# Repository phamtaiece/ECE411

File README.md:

# ECE411
This is for ECE411 practicum. 
The project idea is where we post our idea. Come and contribute and have fun.

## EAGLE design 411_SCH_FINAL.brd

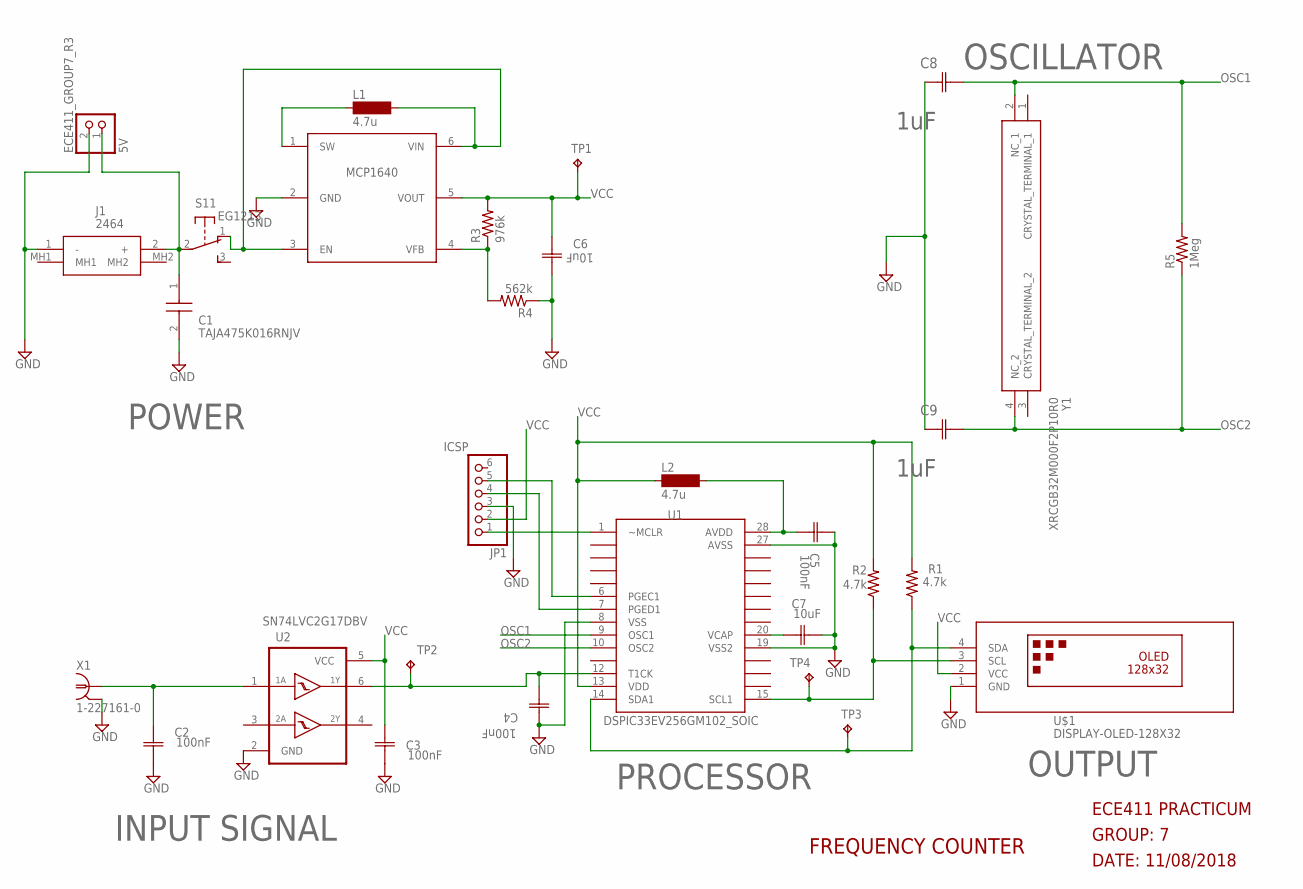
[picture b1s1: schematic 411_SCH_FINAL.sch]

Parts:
C1: TAJA475K016RNJV; CAPPM3216X180N
C2, C3, C4, C5: 100nF; CAPC2013X110N
C6, C7: 10uF; CAPC2013X140N
C8, C9: 1uF; CAPC2013X110N
ECE411_GROUP7_R3: 5V; JST-PH-2-THM-RA; MPN M20-9990246
J1: 2464
JP1: ICSP; 1X06
L1, L2: 4.7u; SM-1206
MCP1: MCP1640; SOP95P270X145-6; MPN MCP1640DT-I/CHY
R1, R2: 4.7k; M2012; MPN CR1206-JW-114ELF
R3: 976k; R0805
R4: 562k; R0805
R5: 1Meg; M0805
S1: EG1213
TP1, TP2, TP3, TP4: TPB1,27; B1,27
U1: DSPIC33EV256GM102_SOIC; SOIC127P1020X265-28; MPN DSPIC33EV256GM102
U2: SN74LVC2G17DBV; SOT23-6; MPN NC7WZ14P6X
U$1: DISPLAY-OLED-128X32; MPN SSD1306
X1: 1-227161-0; AMP_227161
Y1: XRCGB32M000F2P10R0; XRCGB32_F

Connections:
BATT: L1.2, MCP1.3 (EN), MCP1.6 (VIN), S1.1 (O)
GND: C1.2 (-), C2.2 (C2), C3.2 (C2), C4.2 (C2), C5.1 (C1), C6.2 (C2), C7.2 (C2), C8.1 (C1), C9.1 (C1), ECE411_GROUP7_R3.2 (1), J1.1 (-), JP1.3, MCP1.2 (GND), R4.1, U1.8 (VSS), U1.19 (VSS2), U1.27 (AVSS), U2.2 (GND), U$1.1 (GND), X1.2
unnamed: C7.1 (C1), U1.20 (VCAP)
unnamed: C1.1 (+), ECE411_GROUP7_R3.1 (2), J1.2 (+), S1.2
unnamed: R1.1, TP3.TP, U1.14 (SDA1), U$1.4 (SDA)
unnamed: C2.1 (C1), U2.1 (1A), X1.1
unnamed: C5.2 (C2), L2.2, U1.28 (AVDD)
unnamed: L1.1, MCP1.1 (SW)
unnamed: MCP1.4 (VFB), R3.1, R4.2
unnamed: JP1.1, U1.1 (~MCLR)
unnamed: R2.1, TP4.TP, U1.15 (SCL1), U$1.3 (SCL)
unnamed: JP1.4, U1.7 (PGED1)
unnamed: JP1.5, U1.6 (PGEC1)
unnamed: C4.1 (C1), TP2.TP, U1.12 (T1CK), U2.6 (1Y)
OSC1: C8.2 (C2), R5.2, U1.9 (OSC1), Y1.2 (NC_1)
OSC2: C9.2 (C2), R5.1, U1.10 (OSC2), Y1.4 (NC_2)
VCC: C3.1 (C1), C6.1 (C1), JP1.2, L2.1, MCP1.5 (VOUT), R1.2, R2.2, R3.2, TP1.TP, U1.13 (VDD), U2.5 (VCC), U$1.2 (VCC)

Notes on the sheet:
GROUP: 7
DATE: 11/08/2018
FREQUENCY COUNTER
ECE411 PRACTICUM
POWER
INPUT SIGNAL
OUTPUT
PROCESSOR
OSCILLATOR

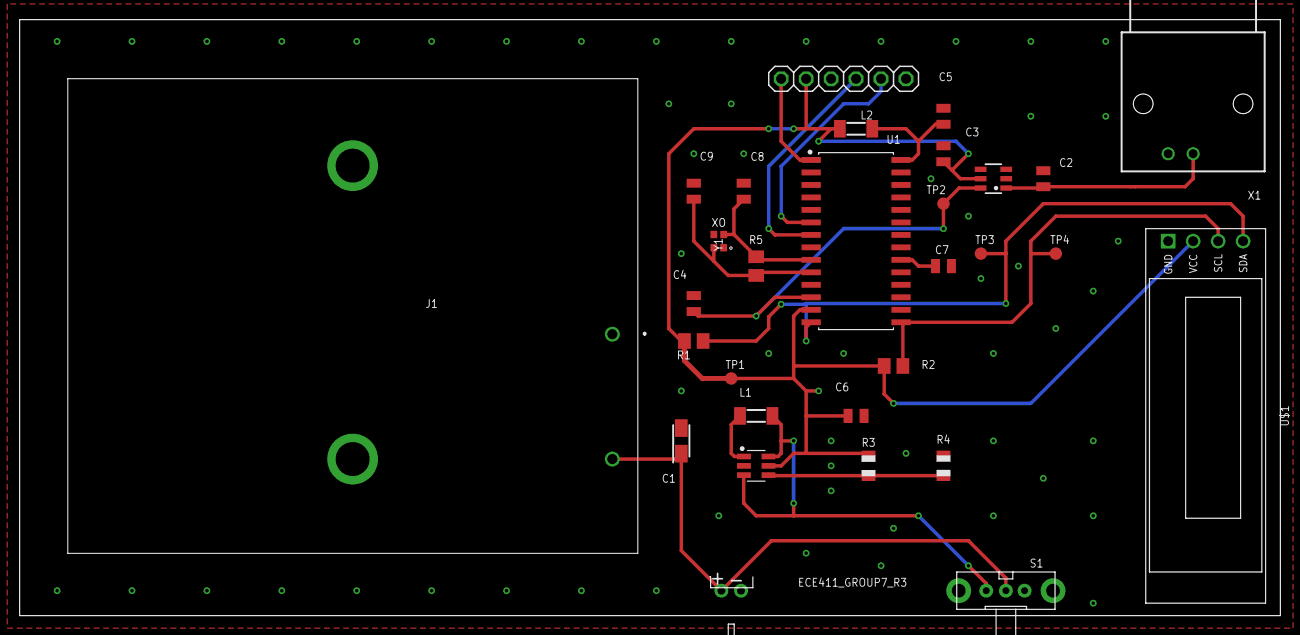
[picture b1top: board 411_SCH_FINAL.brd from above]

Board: 2 copper layers, 128.2 x 60.6 mm, 30 parts (0 on the bottom side), 17 nets.

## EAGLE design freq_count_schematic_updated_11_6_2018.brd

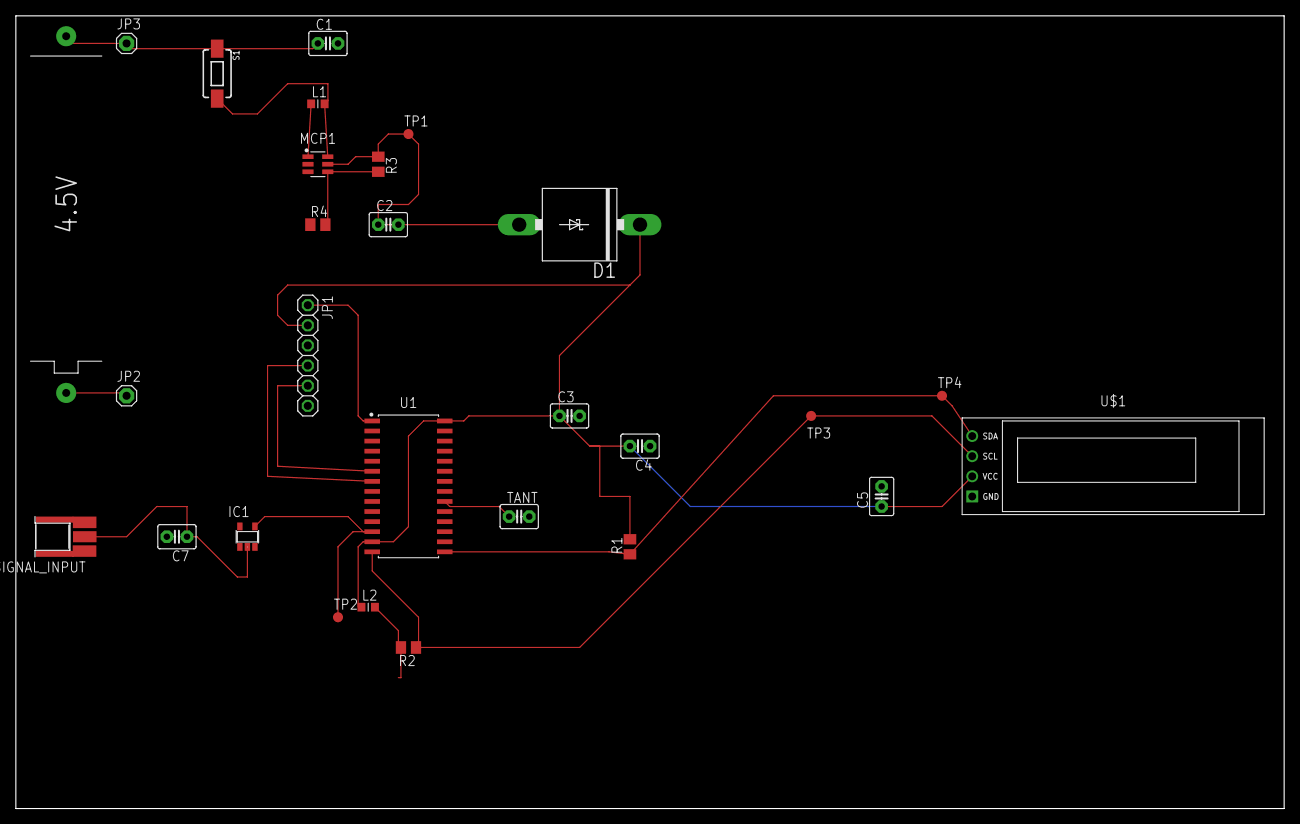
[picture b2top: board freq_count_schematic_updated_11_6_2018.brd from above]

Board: 2 copper layers, 160.0 x 100.0 mm, 28 parts (0 on the bottom side), 15 nets.

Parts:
4.5V: AAA; 12BH412
C1: 4.7u; C2.5-3
C2: 10u; C2.5-3
C3, C7: 1u; C2.5-3
C4, C5: 0.1u; C2.5-3
D1: AG
IC1: 74AHC1G14DBV; SOT23-5
JP1: 1X06
JP2, JP3: 1X01
L1: 4.7u; L0603
L2: L0603
MCP1: MCP1640; SOP95P270X145-6
R1, R2: 10k; M2012
R3: 976k; M2012
R4: 562k; M2012
S1: RS032G05A3SM-SPST-MOMENTARY-SWSMD-1101NE; TACTILE-SWITCH-1101NE
SIGNAL_INPUT: COAX; MMCX-J-P-X-ST-EM1-MKT
TANT: 10u; C2.5-3
TP1, TP2, TP3, TP4: TPB1,27; B1,27
U1: DSPIC33EV256GM102_SOIC; SOIC127P1020X265-28
U$1: DISPLAY-OLED-128X32

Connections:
GND: 4.5V.+, C1.2, C2.2, C3.2, C4.1, C5.2, C7.2, IC1.3, JP1.3, JP2.1, MCP1.2, R4.1, SIGNAL_INPUT.2@1, SIGNAL_INPUT.2@2, SIGNAL_INPUT.2@3, SIGNAL_INPUT.2@4, TANT.2, U1.8, U1.19, U1.27, U$1.1
unnamed: TANT.1, U1.20
unnamed: 4.5V.-, C1.1, JP3.1, S1.1
unnamed: L1.2, MCP1.3, MCP1.6, S1.2
unnamed: C3.1, C4.2, C5.1, D1.C, JP1.2, L2.1, L2.2, R1.2, R2.2, U1.13, U1.28, U$1.2
unnamed: R1.1, TP4.TP, U1.15, U$1.4
unnamed: C7.1, IC1.2, SIGNAL_INPUT.1
unnamed: IC1.4, TP2.TP, U1.12
unnamed: C2.1, D1.A, MCP1.5, R3.1, TP1.TP
unnamed: R2.1, TP3.TP, U1.14, U$1.3
unnamed: L1.1, MCP1.1
unnamed: MCP1.4, R3.2, R4.2
unnamed: JP1.1, U1.1
unnamed: JP1.4, U1.7
unnamed: JP1.5, U1.6

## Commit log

2018-09-29 Create Project idea
2018-09-29 Update Project idea
2018-10-08 Practicum Requirements
    Requirements as specified by Prof Greenburg
2018-10-08 411_Weekly_Checklist
2018-10-08 Delete 411_Group_Timeline (2).gsheet
    didn't mean to upload google sheet
2018-10-08 Group_Timeline_Spreadsheet
2018-10-08 Controller Datasheet
2018-10-09 Create frequency counter
2018-10-11 Create Design goals\
2018-10-11 Create design goals
2018-10-11 Update design goals
2018-10-17 PICkit4 Debugger User Guide
2018-10-17 Understanding I2C
    Excellent document for review about how I2C works
2018-10-18 Design Requirements
    all 4 members have contributed, updated 10-18-2018
2018-10-18 Create readit
2018-10-18 Add files via upload
    LED driver chip built into LED display
2018-10-25 Create Project Description Specification
2018-10-25 Update Project Description Specification
2018-10-29 Portable Frequency Counter Schematic (EAGLE)
    Schematic of our design as of 10-28-2018 in Eagle
2018-11-02 I2C practice
    Our first attempt at using the I2C module
2018-11-08 initial board layout
2018-11-10 Updated BOM with parts available from Mouser
2018-11-15 dsPIC Oscillator layout
2018-11-25 Create Block diagram
2018-12-01 MOST RECENT SCHEMATIC
    as of 12/1/2018
2018-12-04 OLED code for SSD1306
    OLED code for SSD1306 using PIC18 microcontroller. We should be able to modify this slightly to implement it on our chip
2018-12-05 Add files via upload
    Code for OLED SSD1306 and I2C

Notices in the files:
parts and their libraries:
diy-modules: Released under the Creative Commons Attribution 4.0 International License: http://creativecommons.org/licenses/by/4.0
